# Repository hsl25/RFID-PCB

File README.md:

**RFID PCB Project**

This project was part of a design task carried out in 1st year at the University of Southampton.

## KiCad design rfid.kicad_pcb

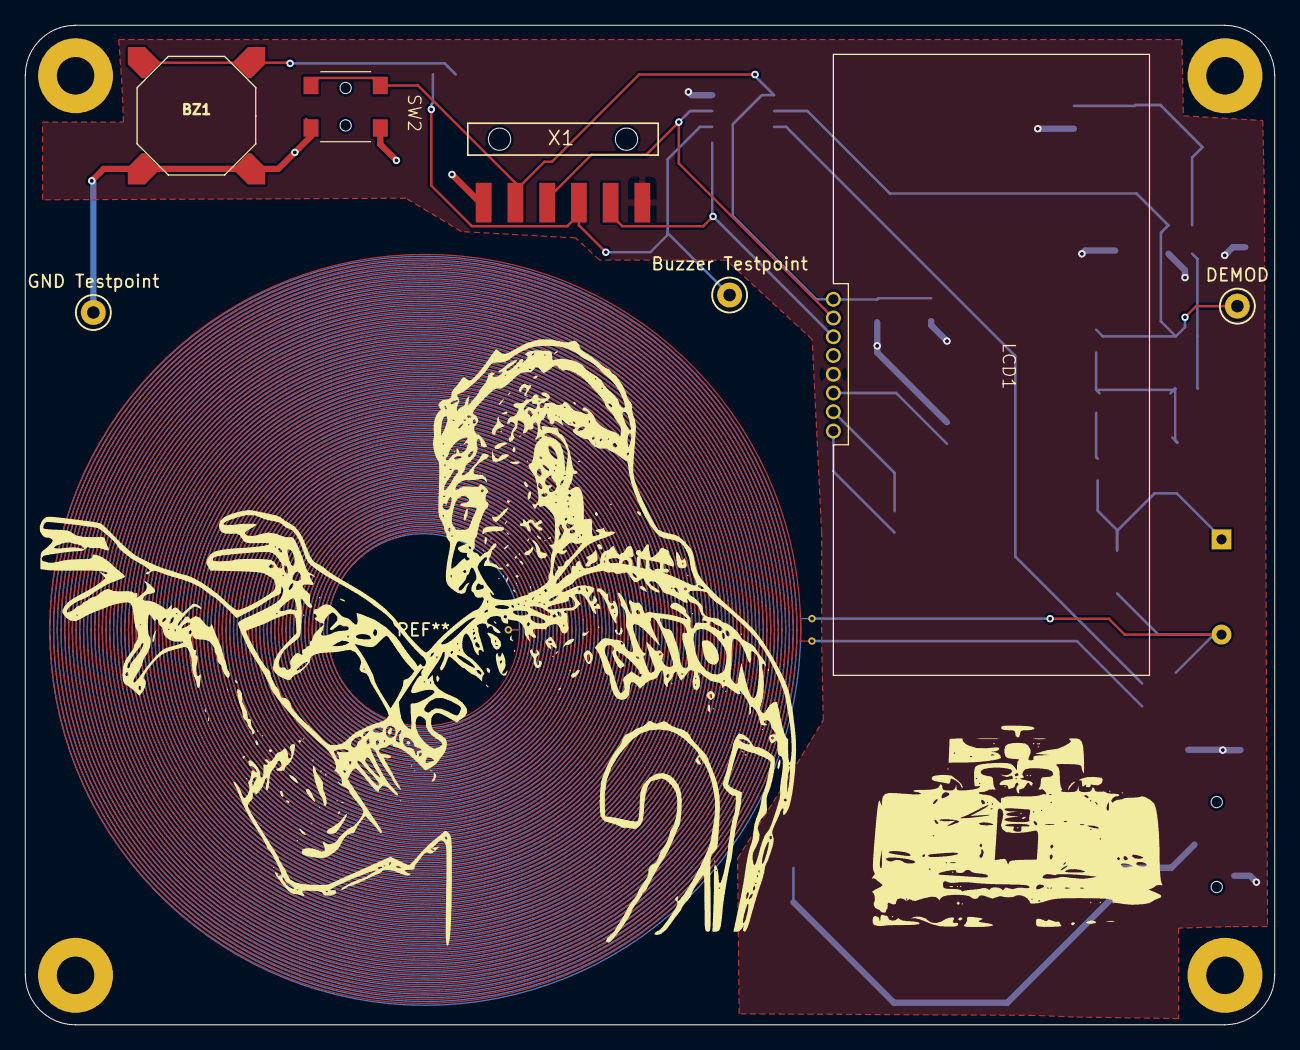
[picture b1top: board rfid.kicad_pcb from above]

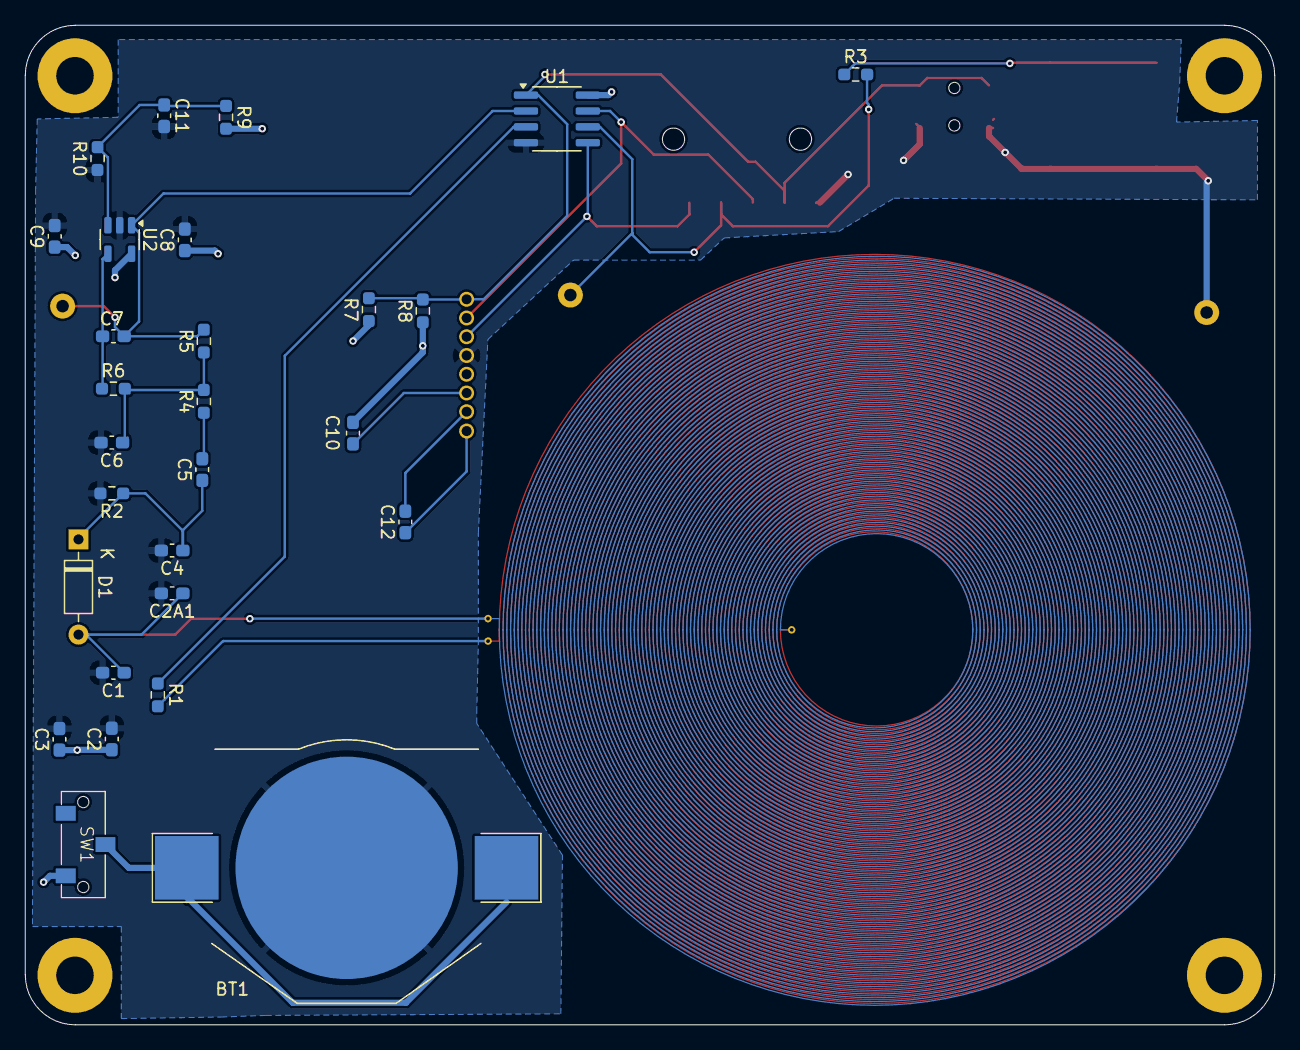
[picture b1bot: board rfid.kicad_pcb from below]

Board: 2 copper layers, 100.0 x 80.0 mm, 40 parts (28 on the bottom side), 19 nets.

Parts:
BT1: BatteryHolder_Keystone_3002_1x2032
BZ1: Buzzer
Buzzer Testpoint: TestPoint; TestPoint_Keystone_5000-5004_Miniature
C1: 10nF; C_0603_1608Metric_Pad1.08x0.95mm_HandSolder
C2, C8: 10uF; C_0603_1608Metric_Pad1.08x0.95mm_HandSolder
C2A1: C_0603_1608Metric_Pad1.08x0.95mm_HandSolder
C3, C5, C9, C11: 100nF; C_0603_1608Metric_Pad1.08x0.95mm_HandSolder
C4: 1nF; C_0603_1608Metric_Pad1.08x0.95mm_HandSolder
C6: 4.7nF; C_0603_1608Metric_Pad1.08x0.95mm_HandSolder
C7: 10pF; C_0603_1608Metric_Pad1.08x0.95mm_HandSolder
C10, C12: C; C_0603_1608Metric_Pad1.08x0.95mm_HandSolder
Coil1: Antony_1
D1: 1N4148; D_DO-35_SOD27_P7.62mm_Horizontal
DEMOD: TestPoint; TestPoint_Keystone_5000-5004_Miniature
GND Testpoint: TestPoint; TestPoint_Keystone_5000-5004_Miniature
H1, H2, H3, H4: MountingHole; MountingHole_3mm_Pad
LCD1: NHD-C0216CiZ-FN-FBW-3V
R1: 100; R_0603_1608Metric_Pad0.98x0.95mm_HandSolder
R2: 470k; R_0603_1608Metric_Pad0.98x0.95mm_HandSolder
R3: 1k; R_0603_1608Metric_Pad0.98x0.95mm_HandSolder
R4: 6.8k; R_0603_1608Metric_Pad0.98x0.95mm_HandSolder
R5: 680k; R_0603_1608Metric_Pad0.98x0.95mm_HandSolder
R6: 47k; R_0603_1608Metric_Pad0.98x0.95mm_HandSolder
R7, R8: 4.7k; R_0603_1608Metric_Pad0.98x0.95mm_HandSolder
R9, R10: 100k; R_0603_1608Metric_Pad0.98x0.95mm_HandSolder
SW1: CL-SB-12A-11T
SW2: 1571262-1
U1: ATtiny25-20SS; SOIC-8_3.9x4.9mm_P1.27mm
U2: OPA842xDBV; SOT-23-5
X1: MH06-1-SMD

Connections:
/BUZZER: Buzzer Testpoint.1, R3.2, U1.6 (PB1), X1.3
/DEMOD: C7.1, DEMOD.1, R5.2, U1.2 (XTAL1/PB3), U2.1
/RFOUT: R1.1, U1.3 (XTAL2/PB4)
/RST: LCD1.1 (RST), R7.2, R8.2, SW2.1, U1.1 (~RESET/PB5), X1.5
/SCL: LCD1.2 (SCL), U1.7 (PB2), X1.4
/SDA: LCD1.3 (SDA), U1.5 (AREF/PB0), X1.2
GND: BT1.2, BZ1.2, C1.2, C2.2, C2A1.2, C3.2, C4.2, C6.2, C8.2, C9.2, C11.2, GND Testpoint.1, LCD1.4 (VSS), R2.2, R10.1, SW2.2, U1.4 (GND), U2.2 (V-), X1.6
unnamed: BT1.1, SW1.2
unnamed: BZ1.1, R3.1
unnamed: C5.2, R4.1
unnamed: C6.1, R4.2, R5.1, R6.2
unnamed: C1.1, C2A1.1, D1.2 (A)
unnamed: C4.1, C5.1, D1.1 (K), R2.1
unnamed: C12.2, LCD1.7 (C+)
unnamed: C12.1, LCD1.8 (C-)
unnamed: C10.2, LCD1.6 (VOUT)
unnamed: C7.2, R6.1, U2.4 (-)
VCC: C2.1, C3.1, C8.1, C9.1, C10.1, LCD1.5 (VDD), R7.1, R8.1, R9.2, SW1.3, U1.8 (VCC), U2.5 (V+), X1.1
VREF: C11.1, R9.1, R10.2, U2.3 (+)

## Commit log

2026-05-30 RFID PCB KiCad files
2026-05-30 Add project description to README
    Added project description for RFID PCB project.
